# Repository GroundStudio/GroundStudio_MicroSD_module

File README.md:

GroundStudio microSD module 
====================================

Get it from [ardushop.ro](https://ardushop.ro/ro/home/2514-modul-microsd-groundstudio.html)

Explore all the GroundStudio products at [GroundStudio.ro](https://groundstudio.ro/)

Description
-------------------
MicroSD adapter module that can be used to connect a microSD card to your project.

Contents
-------------------

* [/Documentation](https://github.com/GroundStudio/GroundStudio_MicroSD_module/tree/main/Documentation) -- Contains documentation written during creation of this repository, with readme.md index of its own!
* [/Firmware](https://github.com/GroundStudio/GroundStudio_MicroSD_module/tree/main/Firmware) -- Firmware (bootloaders, etc)
* [/Hardware](https://github.com/GroundStudio/GroundStudio_MicroSD_module/tree/main/Hardware) -- Schematics, layout.
* [/Libraries](https://github.com/GroundStudio/GroundStudio_MicroSD_module/tree/main/Libraries) -- Arduino/CircuitPython libraries. 
* [/Tools](https://github.com/GroundStudio/GroundStudio_MicroSD_module/tree/main) -- Tools needed for compiling, uploading bootloader, etc.

Versions
-------------------
*(Not all tags shown)*
* [V0.2] Initial version

License
-------------------

This is released under the [Attribution-ShareAlike 4.0 International (CC BY-SA 4.0)](https://creativecommons.org/licenses/by-sa/4.0/) license. 
**You are welcome to use this for commercial purposes.**

Please consider contributing back to this project or others to help the open-source hardware community continue to thrive and grow! 

Certifications:

[Open Source Hardware Association](https://certification.oshwa.org/ro000013.html)   
   
[
](https://certification.oshwa.org/ro000013.html)

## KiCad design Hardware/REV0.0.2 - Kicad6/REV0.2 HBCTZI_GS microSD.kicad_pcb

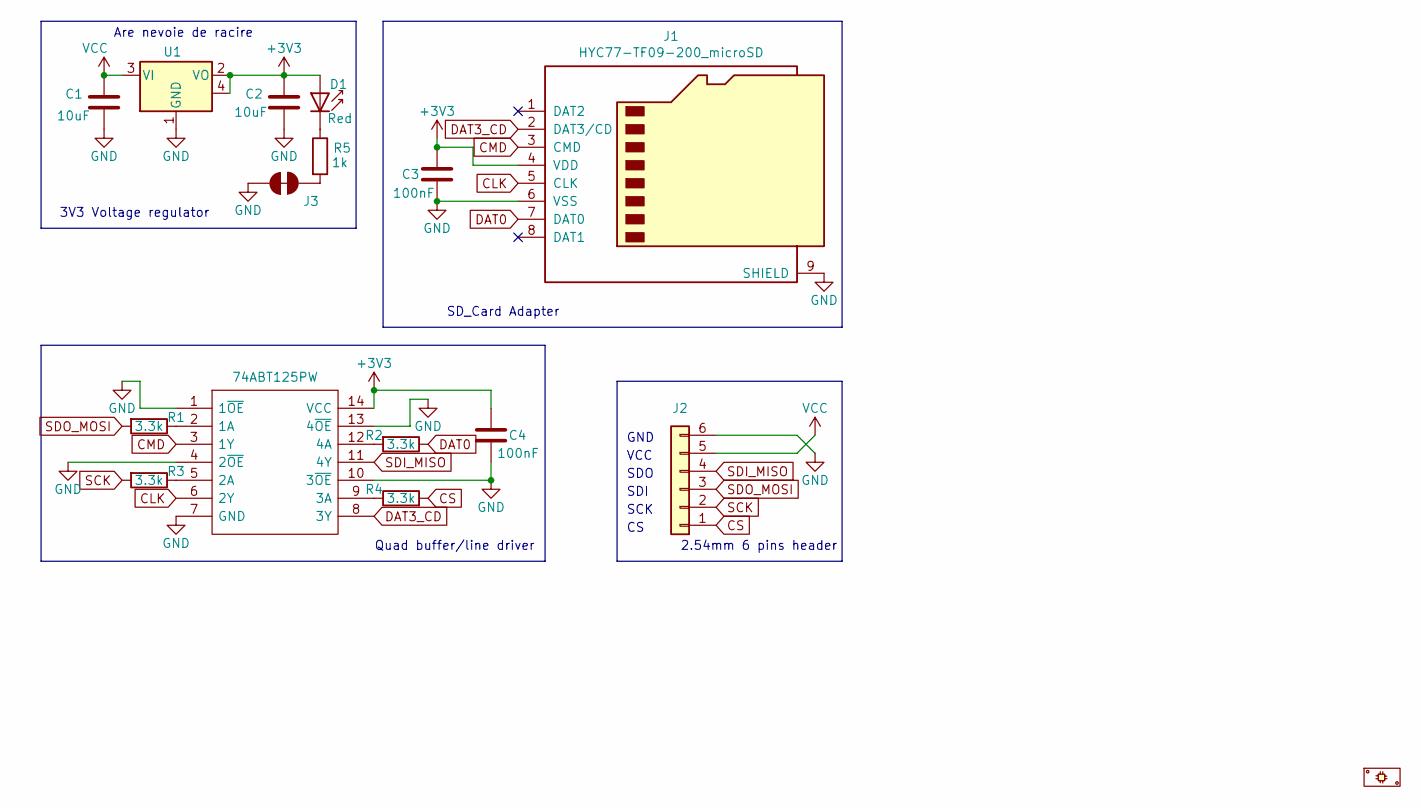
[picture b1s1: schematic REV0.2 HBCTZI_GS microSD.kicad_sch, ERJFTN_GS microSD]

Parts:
C1, C2: C_0402_10uF_10V; C_0402_1005Metric; MPN LDK105CBJ106MVLF; LCSC C386033
C3, C4: C_0402_100nF_10V; C_0402_1005Metric; MPN 0402B104K100CT; LCSC C387941
D1: LED_0402_RED; LED_0402_1005Metric; MPN TZ-P2-0402RTIA1-0.45T; LCSC C779449
IC1: 74ABT125PW; SOT402-1; MPN 74ABT125PW,118; LCSC C458207
J1: HYC77-TF09-200_microSD; HYC77-TF09-200; MPN HYC77-TF09-200; LCSC C341092
J2: Conn_01x06 Male Right Angle; PinHeader_1x06_P2.54mm_Vertical_Male; MPN C56816; LCSC C56816
J3: PWR LED DISABLE; SolderJumper_NC
P1: PCB; MPN HBCTZI_GS_PCB
R1, R2, R3, R4: R_0402_3.3k; R_0402_1005Metric; MPN RC-02W3301FT; LCSC C310224
R5: R_0402_1k; R_0402_1005Metric; MPN RC-02W1001FT; LCSC C226166
U1: SOT-223 AMS1117-3.3; SOT-223; MPN AMS1117-3.3; LCSC C347222

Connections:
+3V3: C2.2, C3.1, C4.1, D1.2 (A), IC1.14 (VCC), J1.4 (VDD), U1.2 (VO), U1.4
CLK: IC1.6 (2Y), J1.5 (CLK)
CMD: IC1.3 (1Y), J1.3 (CMD)
CS: J2.1, R4.2
DAT0: J1.7 (DAT0), R2.1
DAT3_CD: IC1.8 (3Y), J1.2 (DAT3/CD)
GND: C1.1, C2.1, C3.2, C4.2, IC1.1 (1~OE), IC1.4 (2~OE), IC1.7 (GND), IC1.10 (3~OE), IC1.13 (4~OE), J1.6 (VSS), J1.9 (SHIELD), J2.6, J3.2, U1.1 (GND)
unnamed: D1.1 (K), R5.1
unnamed: IC1.2 (1A), R1.1
unnamed: IC1.5 (2A), R3.1
unnamed: IC1.9 (3A), R4.1
unnamed: IC1.12 (4A), R2.2
unnamed: J3.1, R5.2
SCK: J2.2, R3.2
SDI_MISO: IC1.11 (4Y), J2.4
SDO_MOSI: J2.3, R1.2
VCC: C1.2, J2.5, U1.3 (VI)

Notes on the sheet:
Are nevoie de racire
GND
2.54mm 6 pins header
SCK
Quad buffer/line driver
3V3 Voltage regulator
VCC
SDI
SD_Card Adapter
SDO

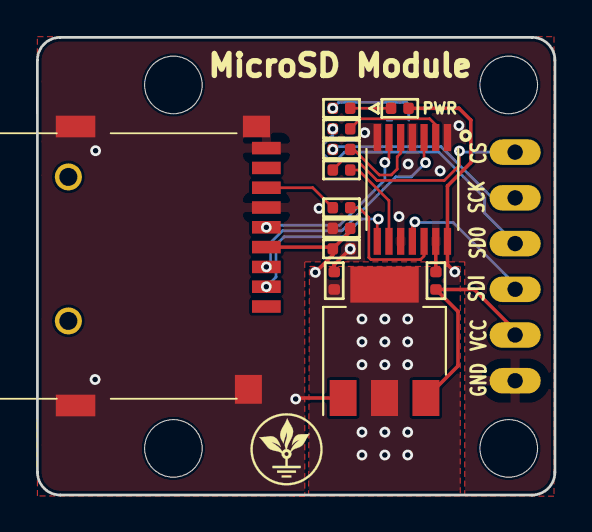
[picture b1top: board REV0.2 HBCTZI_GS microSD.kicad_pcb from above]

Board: 2 copper layers, 28.8 x 25.4 mm, 15 parts (1 on the bottom side), 17 nets.

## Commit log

2023-10-23 - first commit
2023-11-03 - added datasheet
